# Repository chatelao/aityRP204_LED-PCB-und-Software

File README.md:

# Aity Kids 4-LED Board

Dieses Projekt bietet ein einfaches 4-LED-Board an, das mit einem Seeed Studio XIAO RP2040 (oder einem kompatiblen XIAO-Modul) betrieben wird. Es enthält Beispiele sowohl für CircuitPython als auch für den Microsoft MakeCode Maker.

## Hardware-Konfiguration

- **Mikrocontroller**: Seeed Studio XIAO RP2040.
- **NeoPixel-Datenpin**: Verbunden mit **D10** (entspricht **GP3** auf dem RP2040).
- **LED-Matrix**: In den bereitgestellten Beispielen für eine 16x16-Matrix (256 LEDs) konfiguriert.

## Lektionen

1. [Lektion 1: Erste Schritte](./lektion-1/Lektionserläuterung.md)
2. [Lektion 2: Arcade Controller](./lektion-2/README.md)

## Vorbereitung des XIAO RP2040

Um eine neue Firmware (CircuitPython oder MakeCode) auf den XIAO RP2040 zu laden, müssen Sie zuerst in den **Bootloader-Modus** wechseln:

1. Verbinden Sie den XIAO RP2040 über USB mit Ihrem Computer.
2. Drücken und halten Sie die **BOOT**-Taste (beschriftet mit 'B').
3. Während Sie die **BOOT**-Taste gedrückt halten, drücken Sie einmal kurz die **RESET**-Taste (beschriftet mit 'R') oder stecken Sie das USB-Kabel ein.
4. Lassen Sie die **BOOT**-Taste los.
5. Ein neues Laufwerk mit dem Namen `RPI-RP2` sollte auf Ihrem Computer erscheinen.

---

## CircuitPython (CPy) Installation

### 1. CircuitPython-Firmware installieren
1. Laden Sie die neueste CircuitPython-UF2-Datei für den **Seeeduino XIAO RP2040** von [circuitpython.org](https://circuitpython.org/board/seeeduino_xiao_rp2040/) herunter.
2. Wechseln Sie in den Bootloader-Modus (siehe oben), damit das Laufwerk `RPI-RP2` erscheint.
3. Ziehen Sie die heruntergeladene UF2-Datei per Drag-and-Drop auf das Laufwerk `RPI-RP2`.
4. Das Board startet neu und ein neues Laufwerk mit dem Namen `CIRCUITPY` erscheint.

### 2. Bibliotheken installieren
CircuitPython benötigt externe Bibliotheken, um das Beispiel auszuführen.
1. Laden Sie das [CircuitPython Library Bundle](https://circuitpython.org/libraries) herunter.
2. Erstellen Sie einen Ordner namens `lib` auf Ihrem `CIRCUITPY`-Laufwerk, falls dieser noch nicht existiert.
3. Kopieren Sie die folgenden Ordner/Dateien aus dem Bundle in den `lib`-Ordner:
   - `adafruit_neopixel.mpy` (oder den Ordner)
   - `adafruit_imageload` (Ordner)
   - `adafruit_display_text` (falls für zukünftige Erweiterungen benötigt)

### 3. Code bereitstellen
1. Kopieren Sie die Datei `code.py` aus dem Stammverzeichnis dieses Repositories auf das `CIRCUITPY`-Laufwerk.
2. Falls der Code ein Bild benötigt, kopieren Sie `image.png` in das Stammverzeichnis des `CIRCUITPY`-Laufwerks.
3. Das Board lädt den Code automatisch neu und beginnt mit der Ausführung des Skripts.

---

## MakeCode-Installation

Der Microsoft MakeCode Maker bietet einen blockbasierten Editor sowie einen TypeScript-Editor für den RP2040.

### 1. Projekt öffnen
1. Gehen Sie auf [Microsoft MakeCode Maker](https://maker.makecode.com).
2. Klicken Sie auf **Import** und wählen Sie dann **Import File...** aus.
3. Wählen Sie die Datei `makecode/pxt.json` oder `makecode/main.ts` aus diesem Repository aus.
4. Wenn Sie dazu aufgefordert werden, wählen Sie **Seeed Studio XIAO RP2040** als Ihr Board aus.

### 2. Herunterladen und Flashen
1. Klicken Sie auf die Schaltfläche **Download** im MakeCode-Editor.
2. Es wird eine `.uf2`-Datei generiert.
3. Wechseln Sie in den Bootloader-Modus (siehe oben) auf Ihrem XIAO RP2040.
4. Ziehen Sie die heruntergeladene UF2-Datei per Drag-and-Drop auf das Laufwerk `RPI-RP2`.
5. Das Board startet neu und beginnt sofort mit der Ausführung Ihres MakeCode-Programms.

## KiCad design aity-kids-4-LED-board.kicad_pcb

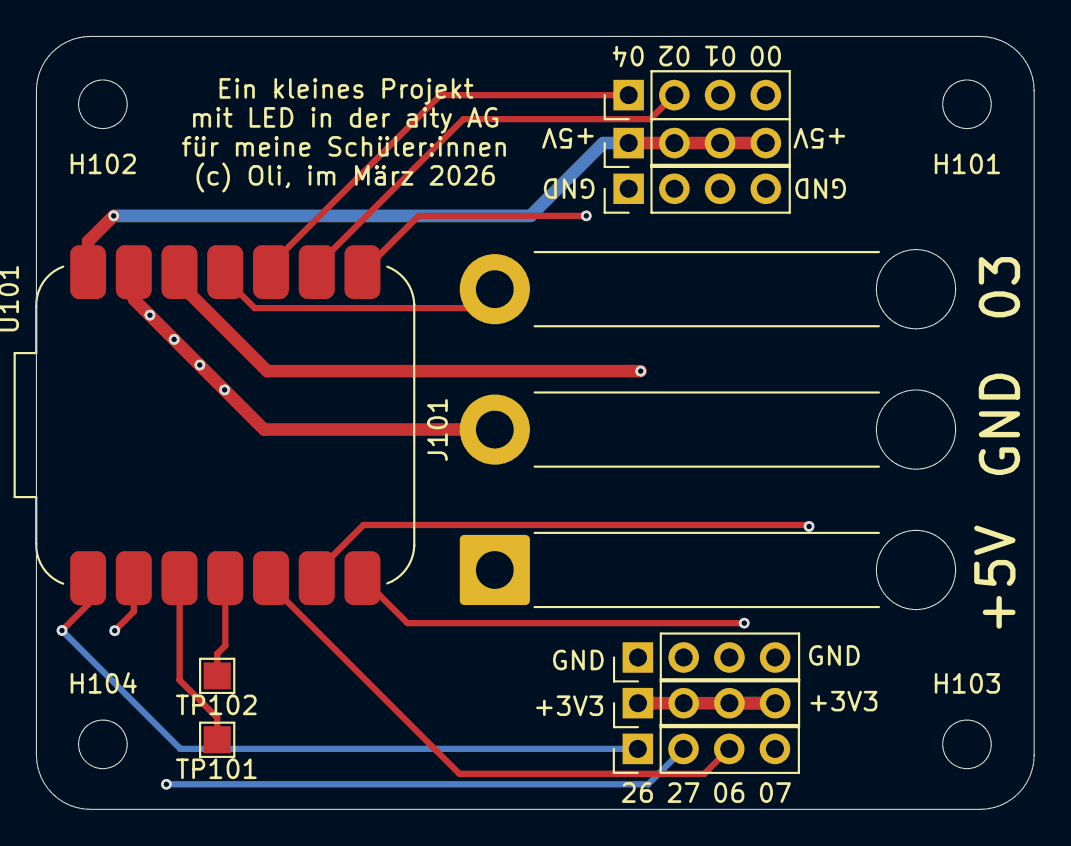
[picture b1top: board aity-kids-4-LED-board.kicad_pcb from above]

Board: 6 copper layers, 55.4 x 42.9 mm, 14 parts (0 on the bottom side), 14 nets.

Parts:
H101, H102, H103, H104: MountingHole; MountingHole_2.7mm_M2.5_DIN965
J101: Conn_01x03; SolderWire-1.5sqmm_1x03_P7.8mm_D1.7mm_OD3.9mm_Relief
J102, J103, J104, J105, J106, J107: Conn_01x04; PinHeader_1x04_P2.54mm_Vertical
TP101, TP102: TestPoint_Small; TestPoint_Pad_1.5x1.5mm
U101: MOUDLE-SEEEDUINO-XIAO-ESP32C3; XIAO_SMD

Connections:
/+3V3: J103.1, J103.2, J103.3, J103.4, U101.12 (3V3)
/+5V: J101.1, J102.1, J102.2, J102.3, J102.4, U101.14 (5V)
/GND: J101.2, J104.1, J104.2, J104.3, J104.4, J105.1, J105.2, J105.3, J105.4, U101.13 (GND)
/GP00: J106.4, U101.7 (A6_TX)
/GP01: J106.3, U101.8 (A7_RX)
/GP02: J106.2, U101.9 (A8_SCK)
/GP03: J101.3, U101.11 (A10_MOSI)
/GP04: J106.1, U101.10 (A9_MISO)
/GP06: J107.3, U101.5 (A4_SDA)
/GP07: J107.4, U101.6 (A5_SCL)
/GP26: J107.1, U101.1 (A0)
/GP27: J107.2, U101.2 (A1)
/GP28: TP101.1, U101.3 (A2)
/GP29: TP102.1, U101.4 (A3)

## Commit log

2026-03-17 Disable DRC and ERC in kibot.yaml
    Updated the preflight section in kibot.yaml to set enabled: false for
    both erc and drc. This ensures that these checks are skipped during
    KiBot execution.
2026-03-17 Add minimal MakeCode Maker sketch for Raspberry Pi Pico
    - Created /makecode directory.
    - Added pxt.json with basic Maker target configuration and 'light' extension dependency.
    - Added main.ts with code to drive 256 WS2811 LEDs on GPIO03 (GP3) using a rainbow animation.
    Note: Exact boardId and pin naming conventions for Raspberry Pi Pico in the MakeCode Maker target were difficult to verify via automated search, so common conventions (GP3 for GPIO03) were used.
2026-03-17 Add minimal CircuitPython script to load PNG to NeoPixel matrix
    - Create `code.py` using `adafruit_imageload` and `neopixel`
    - Implement nearest-neighbor scaling for 256x256 image
    - Configure for XIAO ESP32C3 on board.D10
    - Provide support for progressive and zigzag matrix layouts
2026-03-17 docs: add README with installation instructions for XIAO RP2040
    - Include instructions for entering bootloader mode on the XIAO RP2040.
    - Detail CircuitPython installation and library setup.
    - Detail Microsoft MakeCode Maker setup and project import.
    - Document hardware configuration and NeoPixel data pin mapping.
2026-03-26 Move KiCad project files to /kicad and update CI workflow
    - Created /kicad directory
    - Moved .kicad_pro, .kicad_sch, and .kicad_pcb files to /kicad
    - Updated .github/workflows/kicad-checks.yml to search for projects and run KiBot in the /kicad directory
2026-03-26 Translate README.md to Swiss Standard German
    The entire README.md has been translated into Swiss Standard German (Schweizer Hochdeutsch), following Swiss orthographic conventions (e.g., avoiding 'ß'). All technical terms and sections have been 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
2026-03-26 Add Lesson 1 (LED Basics) with example scripts and documentation.
    This commit introduces the `/lektion-1` directory, containing:
    - `Lektionserläuterung.md`: German lesson explanation.
    - Five CircuitPython example scripts (`code.00_...` to `code.20_...`) for learning LED control and button interaction.
    - The scripts follow a sequential order and are intended to be renamed to `code.py` for execution.
2026-03-26 Link Lektion 1 in README and create Lektion 2 placeholder
    - Added "Lektionen" section to the root README.md with links to Lektion 1 and Lektion 2.
    - Created `lektion-2/` directory and `lektion-2/README.md` placeholder.
2026-06-28 Add title to README for Christmas Run & Jump
2026-06-28 Add external button and game titles to README
2026-06-28 Add external button and sound to README
2026-06-28 feat: add arcade controller integration and exercises for lesson 2
    - Created code.00_joystick_print.py for hardware testing.
    - Created code.01_pixel_move.py for matrix interaction.
    - Created code.10_mini_game.py as a final project.
    - Updated lektion-2/README.md with wiring guide and exercise descriptions.
    - Updated root README.md to include lesson 2.
    - Ensured compliance with Swiss Standard German (no 'ss').
2026-06-28 Rename image.png to wiring_1.png
2026-06-28 Revise arcade joystick pin assignments
    Updated the pin assignments for the arcade joystick connections to the XIAO RP2040.
2026-06-28 Add joystick pin mapping to README
2026-06-30 Add ASCII-Pinout drawing to joystick test and fix README inconsistency
    - Added an ASCII wiring diagram to `lektion-2/code.00_joystick_print.py` illustrating the connection between the XIAO RP2040 and the arcade joystick.
    - Corrected the pinout table in `lektion-2/README.md` to align with the actual pin assignments used in the code (D0, D1, D2, D3).
    - Ensured consistency between documentation and functional scripts.
2026-06-30 docs(lektion-2): add ASCII pinout diagram and correct joystick mappings
    - Added an ASCII-Pinout drawing to `lektion-2/code.00_joystick_print.py` to visualize the XIAO RP2040 and joystick wiring.
    - Corrected the pin mapping in `code.00_joystick_print.py`, `code.01_pixel_move.py`, and `code.10_mini_game.py` to align with the authoritative documentation in the README:
    - Oben (Up): D0
    - Unten (Down): D1
    - Links (Left): D4
    - Rechts (Right): D5
2026-06-30 Fix table formatting in README.md
2026-06-30 Update README with joystick pinout image
    Added a joystick pinout image to the README.
2026-06-30 Update joystick pinout image in README
2026-06-30 Fix image formatting in README.md
    Removed unnecessary line break between images in the README.
2026-06-30 Reorder joystick pin table in README.md
2026-06-30 Correct case of joystick directions in README
